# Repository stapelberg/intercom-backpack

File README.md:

# Intercom MQTT Backpack

See https://michael.stapelberg.ch/posts/2021-03-13-smart-intercom-backpack/

## Components

### tinypico-mqtt-nuki/

ESP32 (TinyPICO) firmware that bridges the BTicino SCS bus and a Nuki Opener
to MQTT. Listens for door-station ring telegrams, drives the Nuki opener (or
the local relay), and exposes everything as MQTT topics.

#### MQTT topics

Published by the doorbell:

| Topic                           | Payload                                                | Notes                  |
|---------------------------------|--------------------------------------------------------|------------------------|
| `doorbell/status`               | `online` / `offline`                                   | retained, LWT          |
| `doorbell/heartbeat`            | `{"uptime_s":N,"rssi":N,"silent":bool}`                | every 60 s             |
| `doorbell/events/scs`           | hex-encoded 7-byte SCS telegram (e.g. `a8 91 03 60 …`) | every detected frame   |
| `doorbell/events/ring`          | `house` or `floor`                                     | one per ring event     |
| `doorbell/silent_state`         | `on` / `off`                                           | retained, doorbell echo |
| `doorbell/debug/suppressed`     | `nukiRing` / `floorRingNuki`                           | when silent suppressed |
| `doorbell/debug/nukiring`       | `ring`                                                 | after Nuki yellow pulse |
| `doorbell/debug/doorunlock`     | `doorunlock`                                           | after relay pulse      |
| `doorbell/debug/floorring`      | `low` / `high`                                         | after floor ring debounce |

Subscribed by the doorbell (set from anywhere on the LAN):

| Topic                       | Payload                | Effect                                   |
|-----------------------------|------------------------|------------------------------------------|
| `doorbell/cmd/unlock`       | any                    | pulses the door-open relay (500 ms)      |
| `doorbell/debug/cmd/ring`   | any                    | simulates a ring (drives Nuki yellow)    |
| `doorbell/silent`           | `on` / `off` (retained) | suppresses Nuki auto-trigger; rings still observable on `events/ring` |

`doorbell/silent` should be published with the retained flag so the state
survives doorbell reboots:

```
mosquitto_pub -h mqtt.lan -t doorbell/silent -r -m on
```

#### Build and flash on NixOS

Pinned to esp32:esp32 2.0.17, PubSubClient 2.8, TinyPICO Helper Library 1.3.0.

One-time bootstrap (downloads the ESP32 core and the two libraries into
`~/.arduino15` and `~/Arduino`):

```bash
nix-shell -p arduino-cli --run '
  arduino-cli config init --overwrite
  arduino-cli config add board_manager.additional_urls \
    https://espressif.github.io/arduino-esp32/package_esp32_index.json
  arduino-cli core update-index
  arduino-cli core install esp32:esp32@2.0.17
  arduino-cli lib install "PubSubClient@2.8"
  arduino-cli lib install "TinyPICO Helper Library@1.3.0"
'
```

esp32 2.0.17 ships an `esptool.py` whose shebang is `#!/usr/bin/env python`
(not `python3`) and that imports `pyserial`. NixOS provides neither in the
default PATH, so build/flash needs both `arduino-cli` and a
`python3.withPackages [pyserial]` plus a one-line `python` shim:

```bash
mkdir -p ~/.local/share/arduino-pyshim
ln -sf "$(command -v python3)" ~/.local/share/arduino-pyshim/python
```

Build (verify):

```bash
nix-shell -p arduino-cli 'python3.withPackages (ps: [ps.pyserial])' --run '
  PATH=~/.local/share/arduino-pyshim:$PATH \
    arduino-cli compile --fqbn esp32:esp32:tinypico ./tinypico-mqtt-nuki
'
```

Expected: ~760 KB sketch (58 % of program flash), ~45 KB globals (13 % of
DRAM), no warnings.

Flash (TinyPICO usually shows up as `/dev/ttyUSBN` via its CP2104 USB-UART
bridge — check `ls /dev/serial/by-id/`):

```bash
nix-shell -p arduino-cli 'python3.withPackages (ps: [ps.pyserial])' --run '
  PATH=~/.local/share/arduino-pyshim:$PATH \
    arduino-cli upload -p /dev/ttyUSB0 --fqbn esp32:esp32:tinypico ./tinypico-mqtt-nuki
'
```

Access to `/dev/ttyUSB*` requires the user to be in the `dialout` group.

### qt-py-scs2uart/

Adafruit QT Py firmware that decodes SCS bus signals and forwards them as
9600-baud UART to whatever sits behind it (in this repo, the TinyPICO above).
Same arduino-cli mechanics as the tinypico build, different board package
(this one has not been re-validated on NixOS in 2026):

```bash
nix-shell -p arduino-cli --run '
  arduino-cli config add board_manager.additional_urls \
    https://www.adafruit.com/package_adafruit_index.json
  arduino-cli core update-index
  arduino-cli core install adafruit:samd
  arduino-cli compile --fqbn adafruit:samd:adafruit_qtpy_m0 ./qt-py-scs2uart
'
```

### kicad-backpack/

A board that is mounted onto the [Adafruit QT
Py](https://www.adafruit.com/product/4600) (hence “backpack”) and adds 5V/3.3V
conversion for interfacing with a BTicino intercom unit (5V).

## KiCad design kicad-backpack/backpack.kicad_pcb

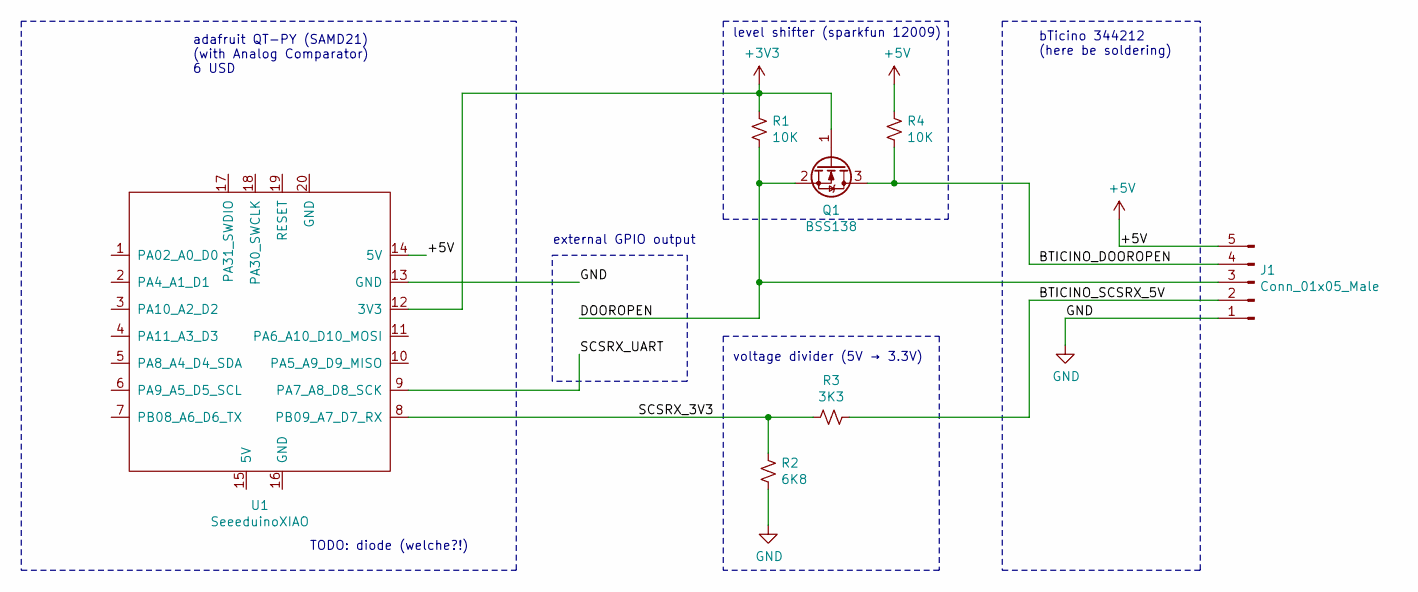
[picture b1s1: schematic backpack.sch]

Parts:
J1: Conn_01x05_Male; PinHeader_1x05_P2.54mm_Horizontal
Q1: BSS138; SOT-23
R1, R4: 10K; R_0603_1608Metric_Pad0.98x0.95mm_HandSolder
R2: 6K8; R_0603_1608Metric_Pad0.98x0.95mm_HandSolder
R3: 3K3; R_0603_1608Metric_Pad0.98x0.95mm_HandSolder
U1: SeeeduinoXIAO; Seeeduino XIAO-MOUDLE14P-2.54-21X17.8MM

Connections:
+3V3: Q1.1 (G), R1.1, U1.12 (3V3)
+5V: J1.5, R4.1, U1.14 (5V)
/BTICINO_DOOROPEN: J1.4, Q1.3 (D), R4.2
/BTICINO_SCSRX_5V: J1.2, R3.1
/DOOROPEN: J1.3, Q1.2 (S), R1.2
/SCSRX_3V3: R2.1, R3.2, U1.8 (PB09_A7_D7_RX)
/SCSRX_UART: U1.9 (PA7_A8_D8_SCK)
GND: J1.1, R2.2, U1.13 (GND)

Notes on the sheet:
adafruit QT-PY (SAMD21) (with Analog Comparator) 6 USD
voltage divider (5V → 3.3V)
level shifter (sparkfun 12009)
bTicino 344212 (here be soldering)
external GPIO output
TODO: diode (welche?!)

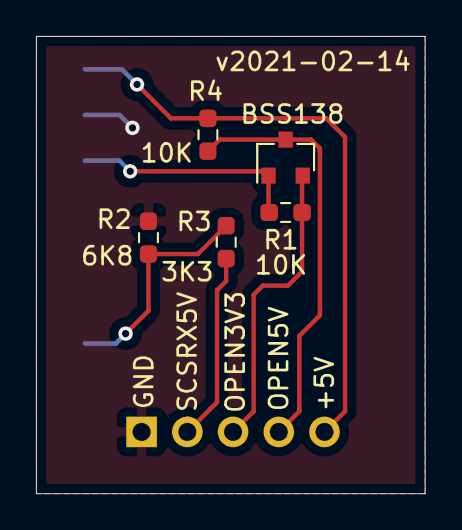
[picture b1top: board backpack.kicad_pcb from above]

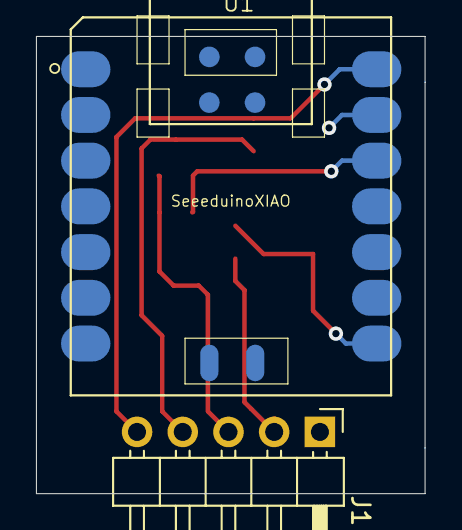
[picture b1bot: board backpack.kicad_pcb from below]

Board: 2 copper layers, 21.6 x 25.4 mm, 7 parts (2 on the bottom side), 7 nets.

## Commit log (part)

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2021-04-13 hook up (and debounce) floor ring, too
2021-04-24 explicitly enable internal pull-down resistor
    Turns out that the opposite of INPUT_PULLUP isn’t INPUT, but INPUT_PULLDOWN.
2026-05-02 increase stack sizes to fix crashes
2026-05-02 attach interrupts early to fix crashes
2026-05-02 disable core 0 WDT to fix MQTT connection
